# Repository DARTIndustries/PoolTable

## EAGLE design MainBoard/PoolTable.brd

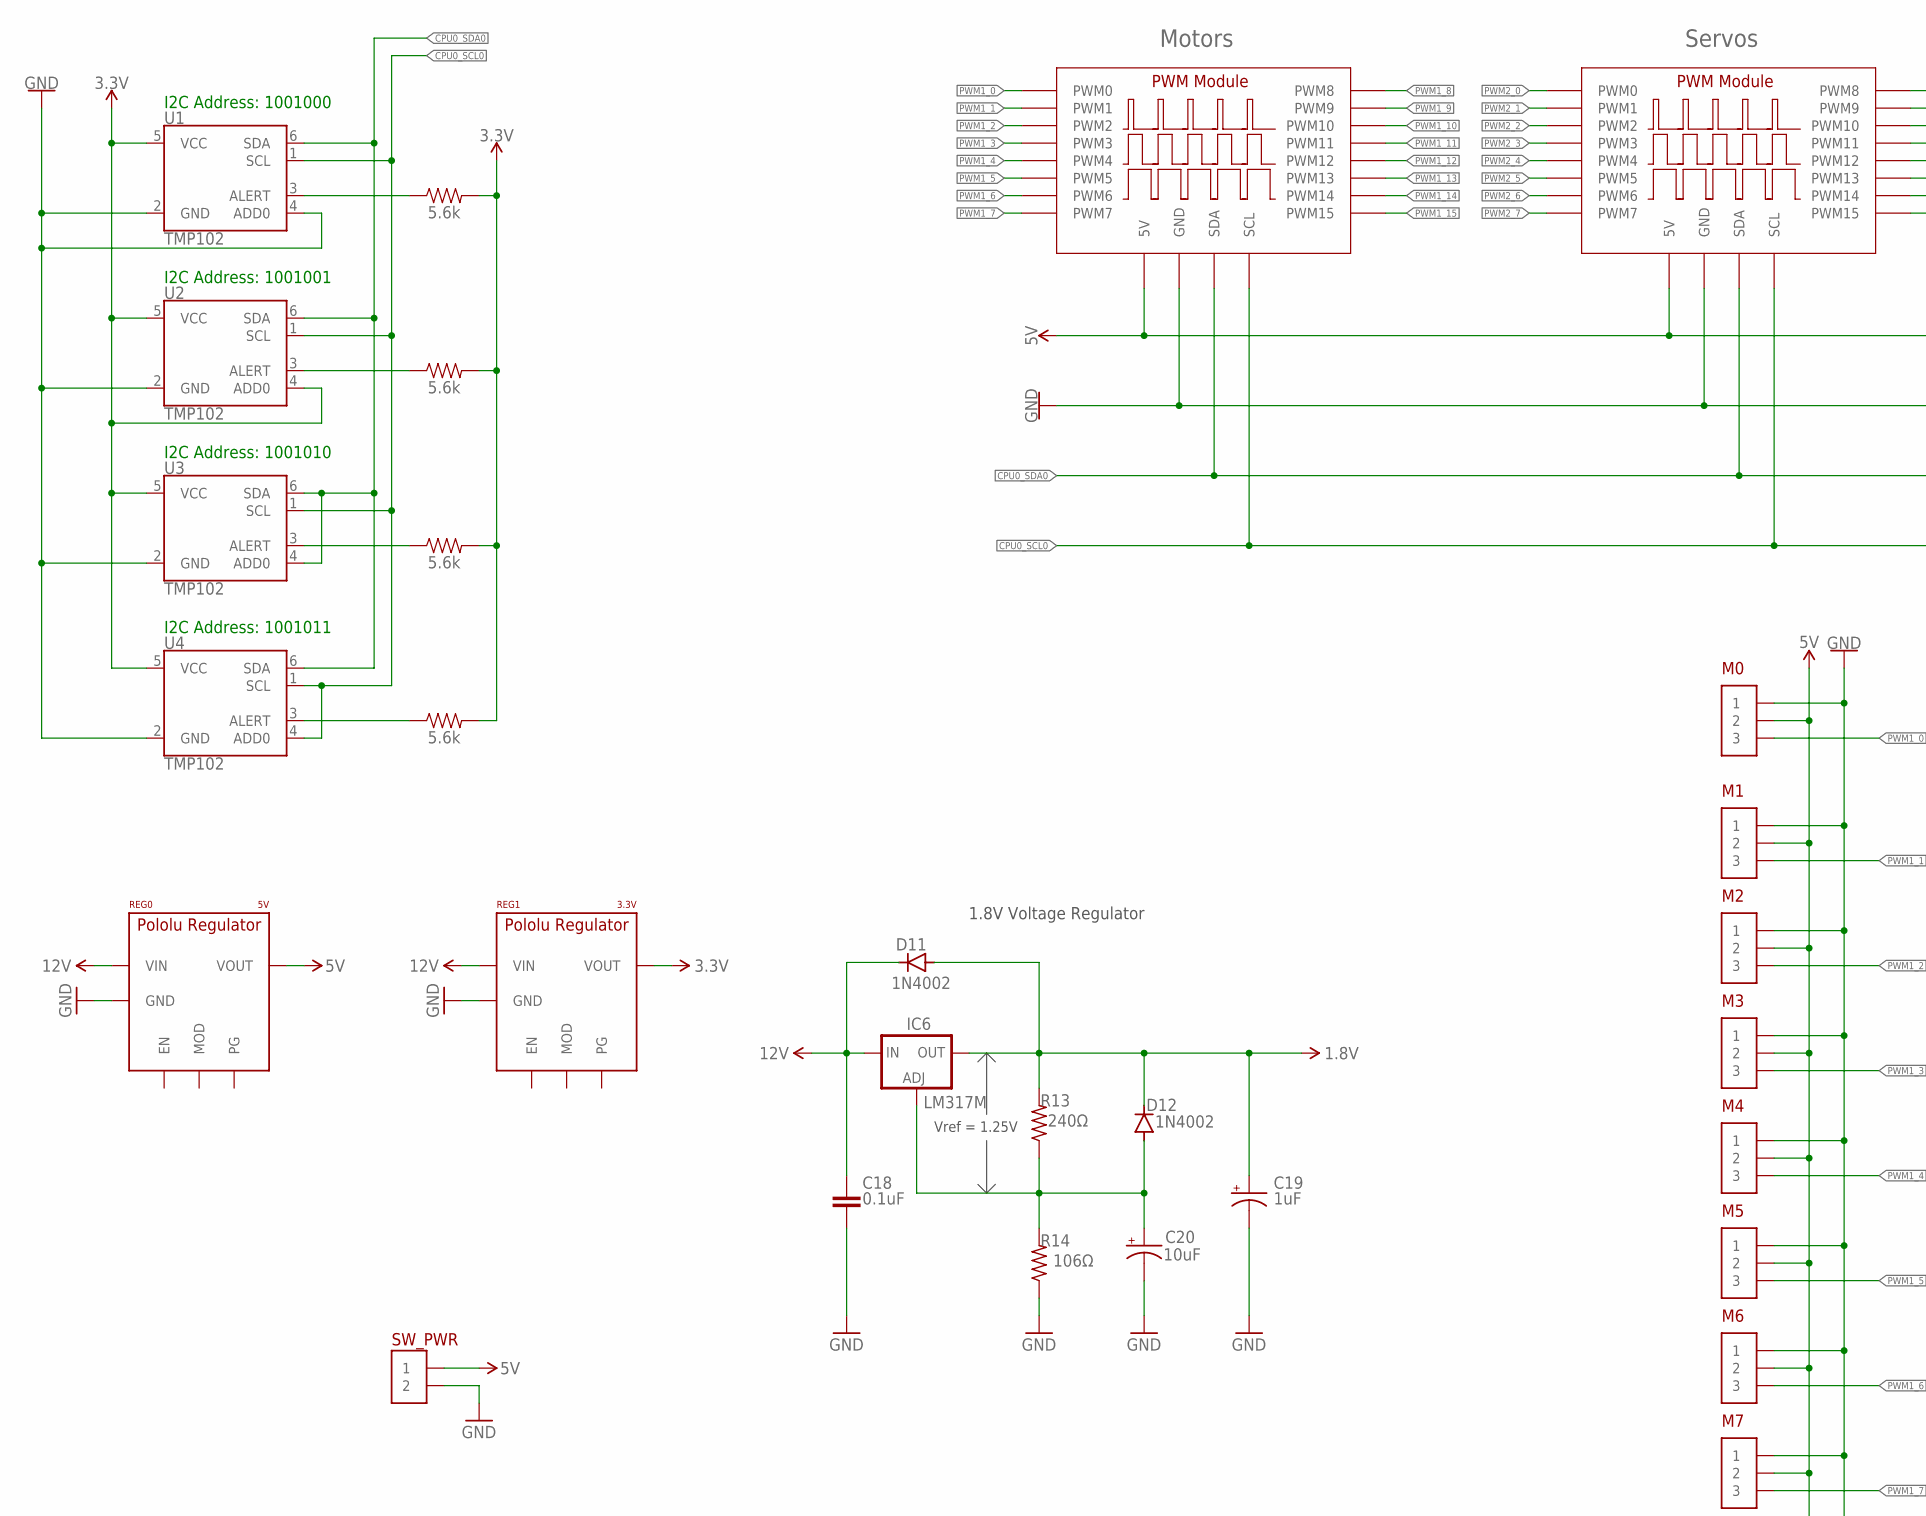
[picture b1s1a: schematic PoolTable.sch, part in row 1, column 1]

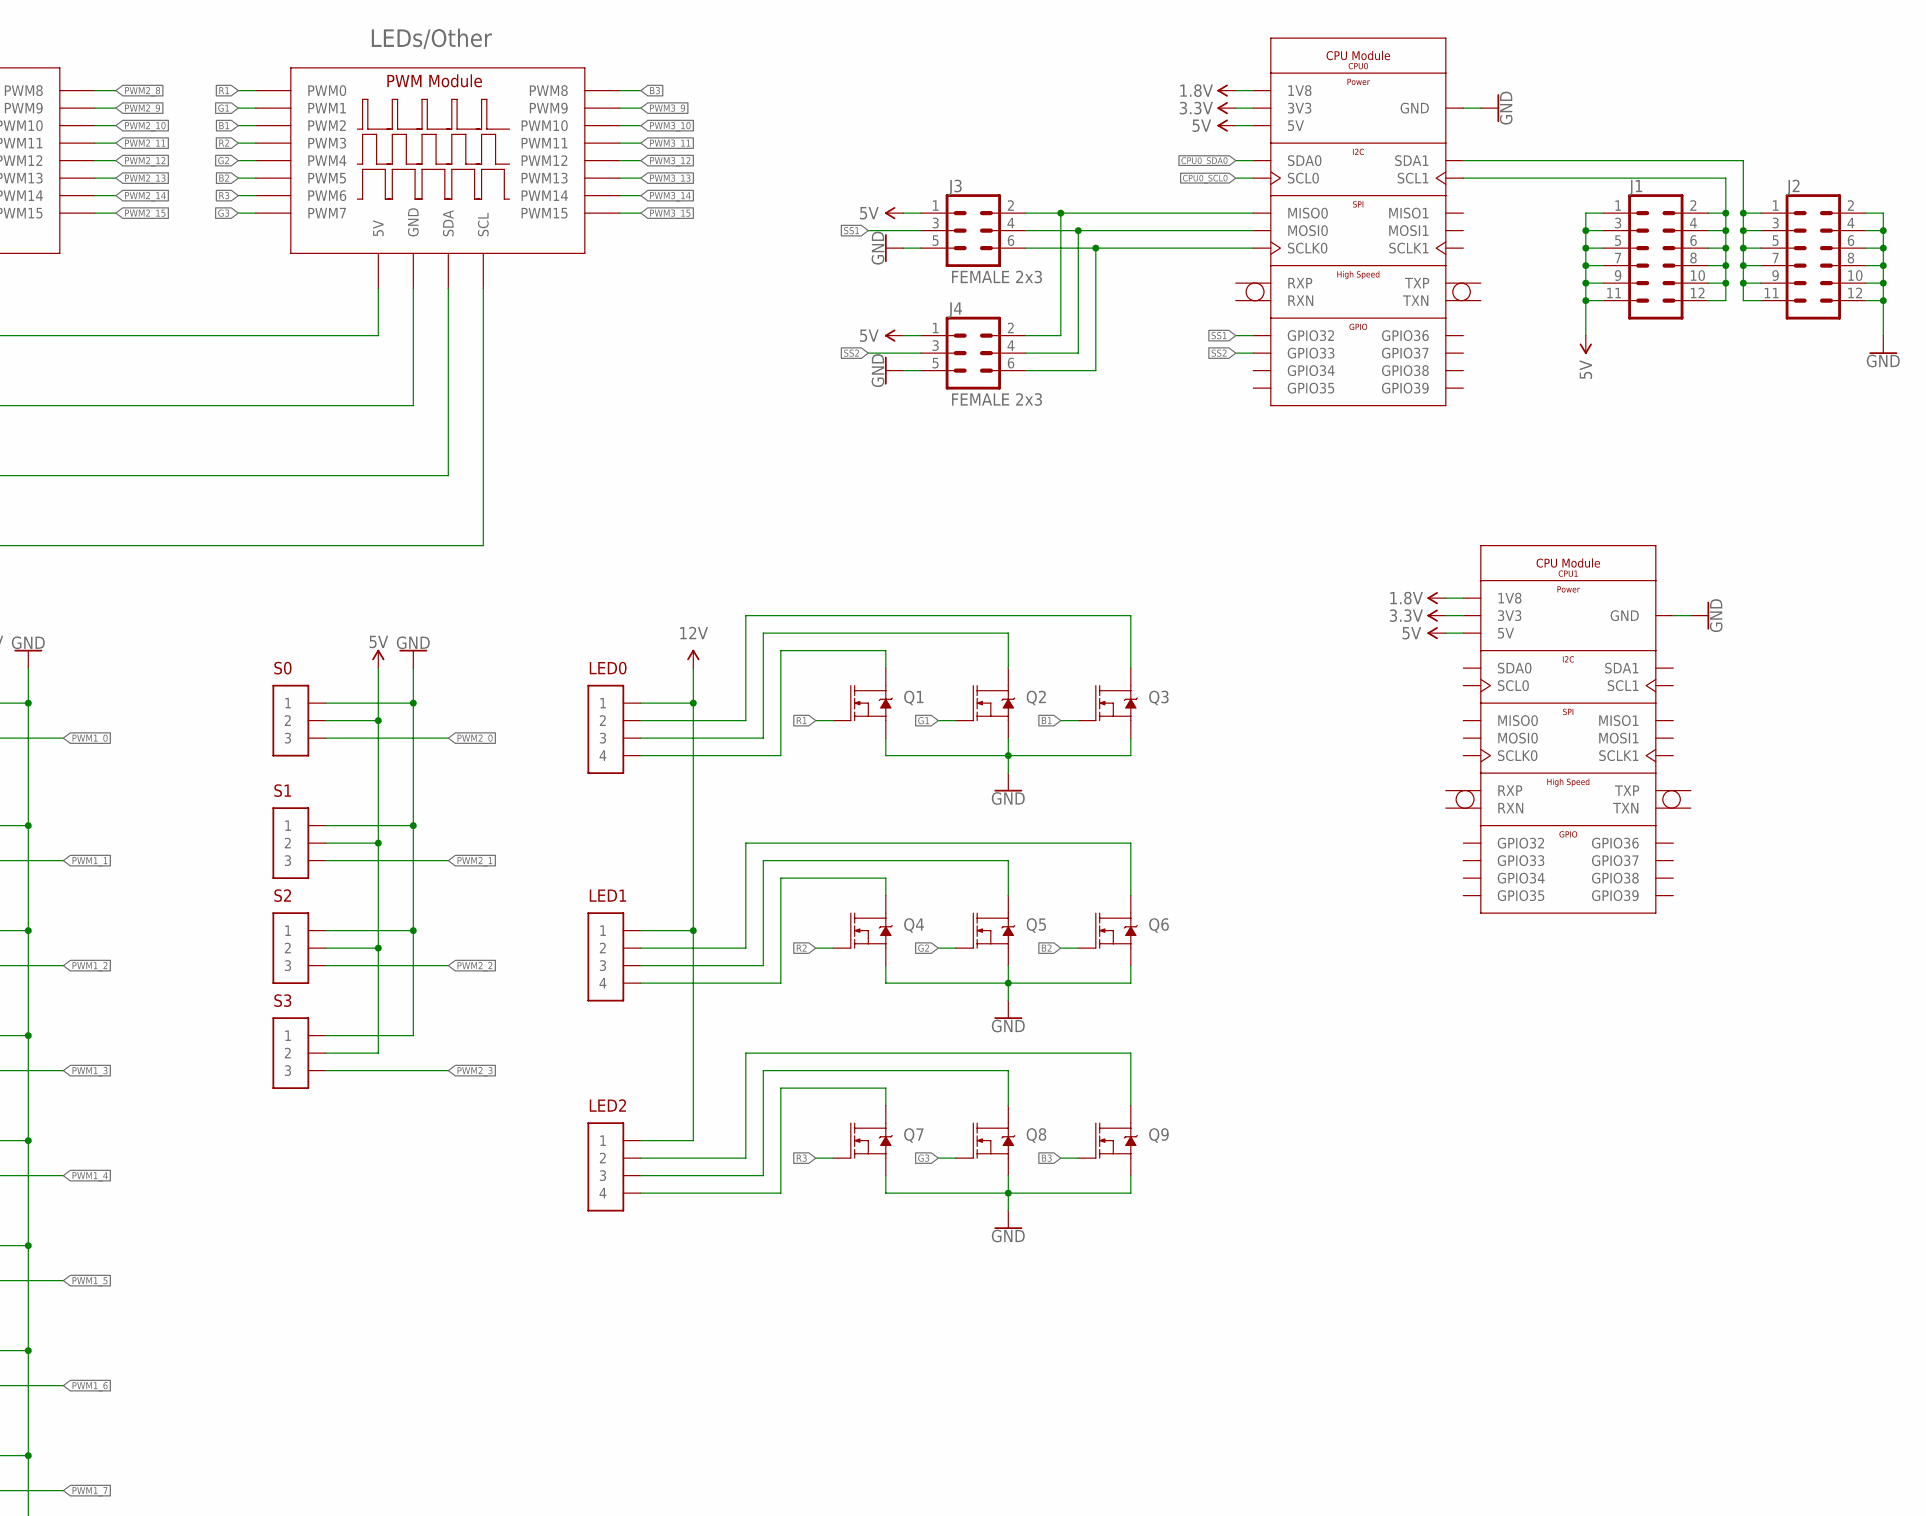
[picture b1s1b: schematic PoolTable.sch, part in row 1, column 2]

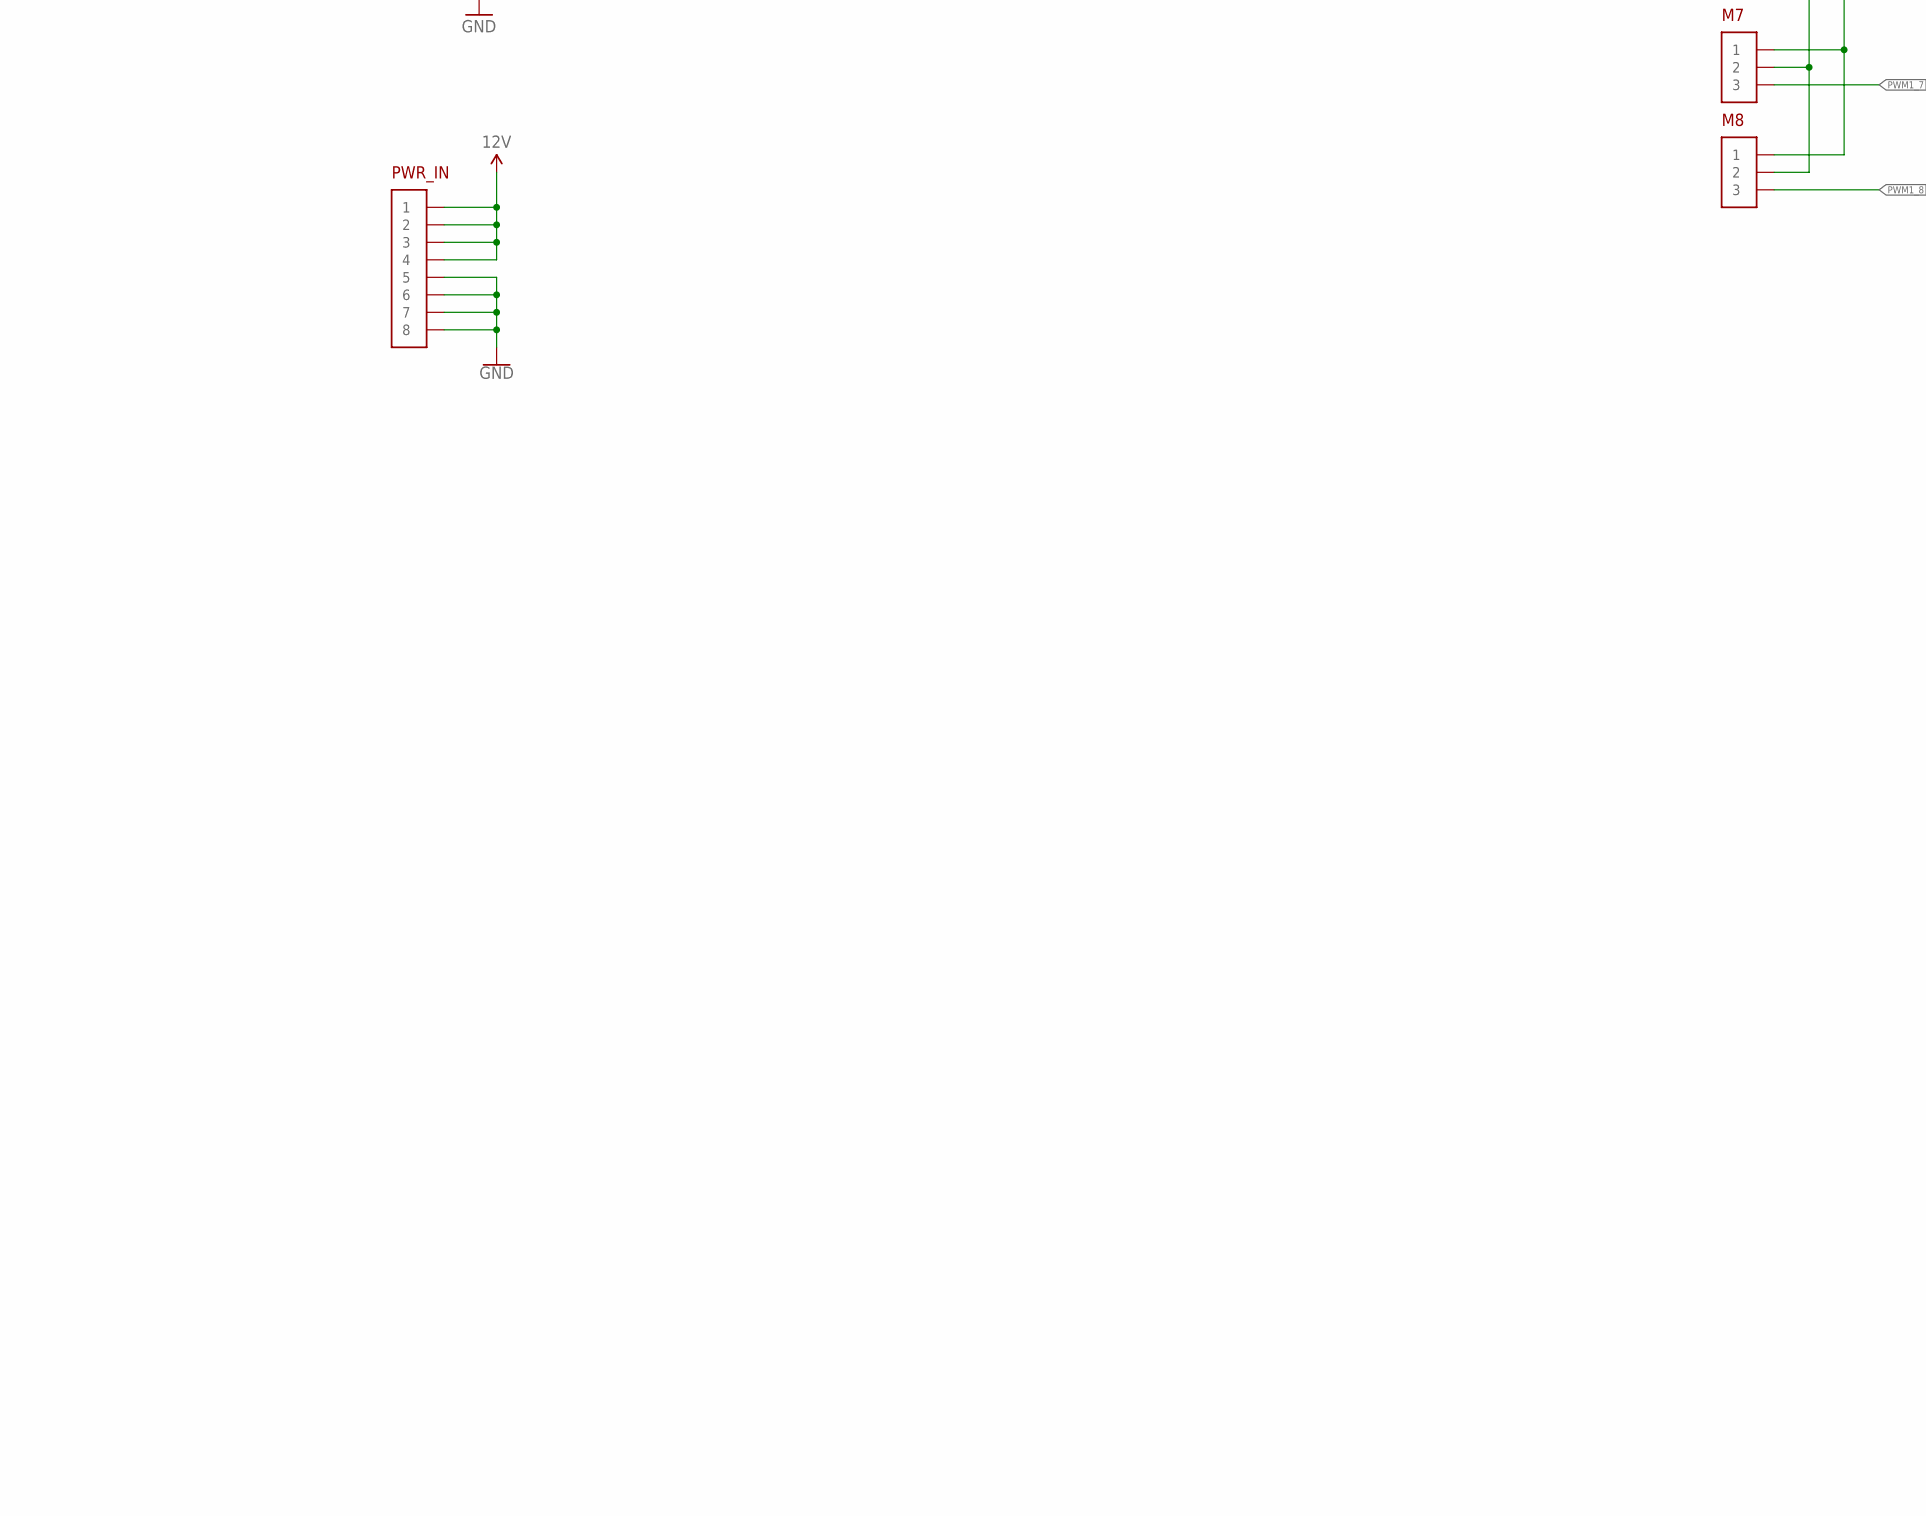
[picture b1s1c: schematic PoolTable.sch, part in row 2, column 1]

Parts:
C18: 0.1uF; C075-052X106
C19: 1uF; 085CS_1AR
C20: 10uF; 085CS_1AR
CPU0, CPU1: CPU_MODULE
D11, D12: 1N4002; DO41-10
IC6: LM317MBSTT3; SOT223; PARTNUMBER LM317M
J1, J2: 2X6 FEMALE; 2X6
J3, J4: FEMALE 2x3; 2X3
LED0, LED1, LED2: MOLEX-ULTRAFIT-1X04VERT; MOLEX-ULTRAFIT-1X04V
M0, M8: MOLEX-ULTRAFIT-1X03-VERT; MOLEX-ULTRAFIT-1X03V
M1, M2, M3, M4, M5, M6, M7: MOLEX-ULTRAFIT-1X03VERT; MOLEX-ULTRAFIT-1X03V
PWM0, PWM1, PWM2: PWM_MODULE
PWR_IN: MOLEX-ULTRAFIT-1X08
Q1, Q2, Q3, Q4, Q5, Q6, Q7, Q8, Q9: 60V/32A/35mΩ; TO220V
R9, R12, R15, R18: 5.6k; 0603
R13: 240Ω; M0805
R14: 106Ω; M0805
REG0: 5V; POLOLU-REG
REG1: 3.3V; POLOLU-REG
S0, S2, S3: MOLEX-ULTRAFIT-1X03VERT; MOLEX-ULTRAFIT-1X03V
S1: MOLEX-ULTRAFIT-1X03-VERT; MOLEX-ULTRAFIT-1X03V
SW_PWR: MOLEX-ULTRAFIT-1X02-HORIZ; MOLEX-ULTRAFIT-1X02H
U1, U2, U3, U4: TMP102; SOT563

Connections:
1.8V: C19.+, CPU0.19 (1V8), CPU1.19 (1V8), D11.A, D12.C, IC6.4 (OUT), R13.2
3.3V: CPU0.20 (3V3), CPU1.20 (3V3), R9.2, R12.2, R15.2, R18.2, REG1.P$4 (VOUT), REG1.P$7 (VOUT), REG1.P$8 (VOUT), U1.5 (VCC), U2.4 (ADD0), U2.5 (VCC), U3.5 (VCC), U4.5 (VCC)
5V: CPU0.18 (5V), CPU1.18 (5V), J1.1, J1.3, J1.5, J1.7, J1.9, J1.11, J3.1, J4.1, M0.P$2 (2), M1.P$2 (2), M2.P$2 (2), M3.P$2 (2), M4.P$2 (2), M5.P$2 (2), M6.P$2 (2), M7.P$2 (2), M8.P$2 (2), PWM0.5V, PWM1.5V, PWM2.5V, REG0.P$4 (VOUT), REG0.P$7 (VOUT), REG0.P$8 (VOUT), S0.P$2 (2), S1.P$2 (2), S2.P$2 (2), S3.P$2 (2), SW_PWR.P$1 (1)
12V: C18.1, D11.C, IC6.3 (IN), LED0.P$1 (1), LED1.P$1 (1), LED2.P$1 (1), PWR_IN.P$1 (1), PWR_IN.P$2 (2), PWR_IN.P$3 (3), PWR_IN.P$4 (4), REG0.P$1 (VIN), REG0.P$14 (VIN), REG0.P$15 (VIN), REG1.P$1 (VIN), REG1.P$14 (VIN), REG1.P$15 (VIN)
B1: PWM1.PWM2, Q3.1 (G)
B2: PWM1.PWM5, Q6.1 (G)
B3: PWM1.PWM8, Q9.1 (G)
CPU0_SCL0: CPU0.15 (SCL0), PWM0.SCL, PWM1.SCL, PWM2.SCL, U1.1 (SCL), U2.1 (SCL), U3.1 (SCL), U4.1 (SCL), U4.4 (ADD0)
CPU0_SDA0: CPU0.13 (SDA0), PWM0.SDA, PWM1.SDA, PWM2.SDA, U1.6 (SDA), U2.6 (SDA), U3.4 (ADD0), U3.6 (SDA), U4.6 (SDA)
G1: PWM1.PWM1, Q2.1 (G)
G2: PWM1.PWM4, Q5.1 (G)
G3: PWM1.PWM7, Q8.1 (G)
GND: C18.2, C19.-, C20.-, CPU0.1 (GND), CPU0.2 (GND), CPU0.3 (GND), CPU0.6 (GND), CPU0.7 (GND), CPU0.10 (GND), CPU0.11 (GND), CPU0.14 (GND), CPU0.17 (GND), CPU0.21 (GND), CPU0.24 (GND), CPU0.27 (GND), CPU0.30 (GND), CPU0.33 (GND), CPU0.37 (GND), CPU1.1 (GND), CPU1.2 (GND), CPU1.3 (GND), CPU1.6 (GND), CPU1.7 (GND), CPU1.10 (GND), CPU1.11 (GND), CPU1.14 (GND), CPU1.17 (GND), CPU1.21 (GND), CPU1.24 (GND), CPU1.27 (GND), CPU1.30 (GND), CPU1.33 (GND), CPU1.37 (GND), J2.2, J2.4, J2.6, J2.8, J2.10, J2.12, J3.5, J4.5, M0.P$1 (1), M1.P$1 (1), M2.P$1 (1), M3.P$1 (1), M4.P$1 (1), M5.P$1 (1), M6.P$1 (1), M7.P$1 (1), M8.P$1 (1), PWM0.GND, PWM1.GND, PWM2.GND, PWR_IN.P$5 (5), PWR_IN.P$6 (6), PWR_IN.P$7 (7), PWR_IN.P$8 (8), Q1.3 (S), Q2.3 (S), Q3.3 (S), Q4.3 (S), Q5.3 (S), Q6.3 (S), Q7.3 (S), Q8.3 (S), Q9.3 (S), R14.1, REG0.P$2 (GND), REG0.P$3 (GND), REG0.P$5 (GND), REG0.P$6 (GND), REG0.P$11 (GND), REG0.P$12 (GND), REG0.P$16 (GND), REG0.P$17 (GND), REG1.P$2 (GND), REG1.P$3 (GND), REG1.P$5 (GND), REG1.P$6 (GND), REG1.P$11 (GND), REG1.P$12 (GND), REG1.P$16 (GND), REG1.P$17 (GND), S0.P$1 (1), S1.P$1 (1), S2.P$1 (1), S3.P$1 (1), SW_PWR.P$2 (2), U1.2 (GND), U1.4 (ADD0), U2.2 (GND), U3.2 (GND), U4.2 (GND)
unnamed: LED0.P$4 (4), Q1.2 (D)
unnamed: LED0.P$3 (3), Q2.2 (D)
unnamed: LED0.P$2 (2), Q3.2 (D)
unnamed: CPU0.12 (SCL1), J1.2, J1.4, J1.6, J1.8, J1.10, J1.12
unnamed: CPU0.16 (SDA1), J2.1, J2.3, J2.5, J2.7, J2.9, J2.11
unnamed: R9.1, U1.3 (ALERT)
unnamed: C20.+, D12.A, IC6.1 (ADJ), R13.1, R14.2
unnamed: LED1.P$4 (4), Q4.2 (D)
unnamed: R12.1, U3.3 (ALERT)
unnamed: LED1.P$3 (3), Q5.2 (D)
unnamed: LED1.P$2 (2), Q6.2 (D)
unnamed: R15.1, U4.3 (ALERT)
unnamed: LED2.P$4 (4), Q7.2 (D)
unnamed: LED2.P$3 (3), Q8.2 (D)
unnamed: R18.1, U2.3 (ALERT)
unnamed: LED2.P$2 (2), Q9.2 (D)
unnamed: CPU0.39 (MISO0), J3.2, J4.2
unnamed: CPU0.40 (MOSI0), J3.4, J4.4
unnamed: CPU0.38 (SCLK0), J3.6, J4.6
PWM1_0: M0.P$3 (3), PWM0.PWM0
PWM1_1: M1.P$3 (3), PWM0.PWM1
PWM1_2: M2.P$3 (3), PWM0.PWM2
PWM1_3: M3.P$3 (3), PWM0.PWM3
PWM1_4: M4.P$3 (3), PWM0.PWM4
PWM1_5: M5.P$3 (3), PWM0.PWM5
PWM1_6: M6.P$3 (3), PWM0.PWM6
PWM1_7: M7.P$3 (3), PWM0.PWM7
PWM1_8: M8.P$3 (3), PWM0.PWM8
PWM1_9: PWM0.PWM9
PWM1_10: PWM0.PWM10
PWM1_11: PWM0.PWM11
PWM1_12: PWM0.PWM12
PWM1_13: PWM0.PWM13
PWM1_14: PWM0.PWM14
PWM1_15: PWM0.PWM15
PWM2_0: PWM2.PWM0, S0.P$3 (3)
PWM2_1: PWM2.PWM1, S1.P$3 (3)
PWM2_2: PWM2.PWM2, S2.P$3 (3)
PWM2_3: PWM2.PWM3, S3.P$3 (3)
PWM2_4: PWM2.PWM4
PWM2_5: PWM2.PWM5
PWM2_6: PWM2.PWM6
PWM2_7: PWM2.PWM7
PWM2_8: PWM2.PWM8
PWM2_9: PWM2.PWM9
PWM2_10: PWM2.PWM10
PWM2_11: PWM2.PWM11
PWM2_12: PWM2.PWM12
PWM2_13: PWM2.PWM13
PWM2_14: PWM2.PWM14
PWM2_15: PWM2.PWM15
PWM3_9: PWM1.PWM9
PWM3_10: PWM1.PWM10
PWM3_11: PWM1.PWM11
PWM3_12: PWM1.PWM12
PWM3_13: PWM1.PWM13
PWM3_14: PWM1.PWM14
PWM3_15: PWM1.PWM15
R1: PWM1.PWM0, Q1.1 (G)
R2: PWM1.PWM3, Q4.1 (G)
R3: PWM1.PWM6, Q7.1 (G)
SS1: CPU0.32 (GPIO32), J3.3
SS2: CPU0.31 (GPIO33), J4.3

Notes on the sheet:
I2C Address: 1001000
I2C Address: 1001001
I2C Address: 1001010
I2C Address: 1001011
Misc Components
1.8V Voltage Regulator
Vref = 1.25V
Motors
Servos
LEDs/Other

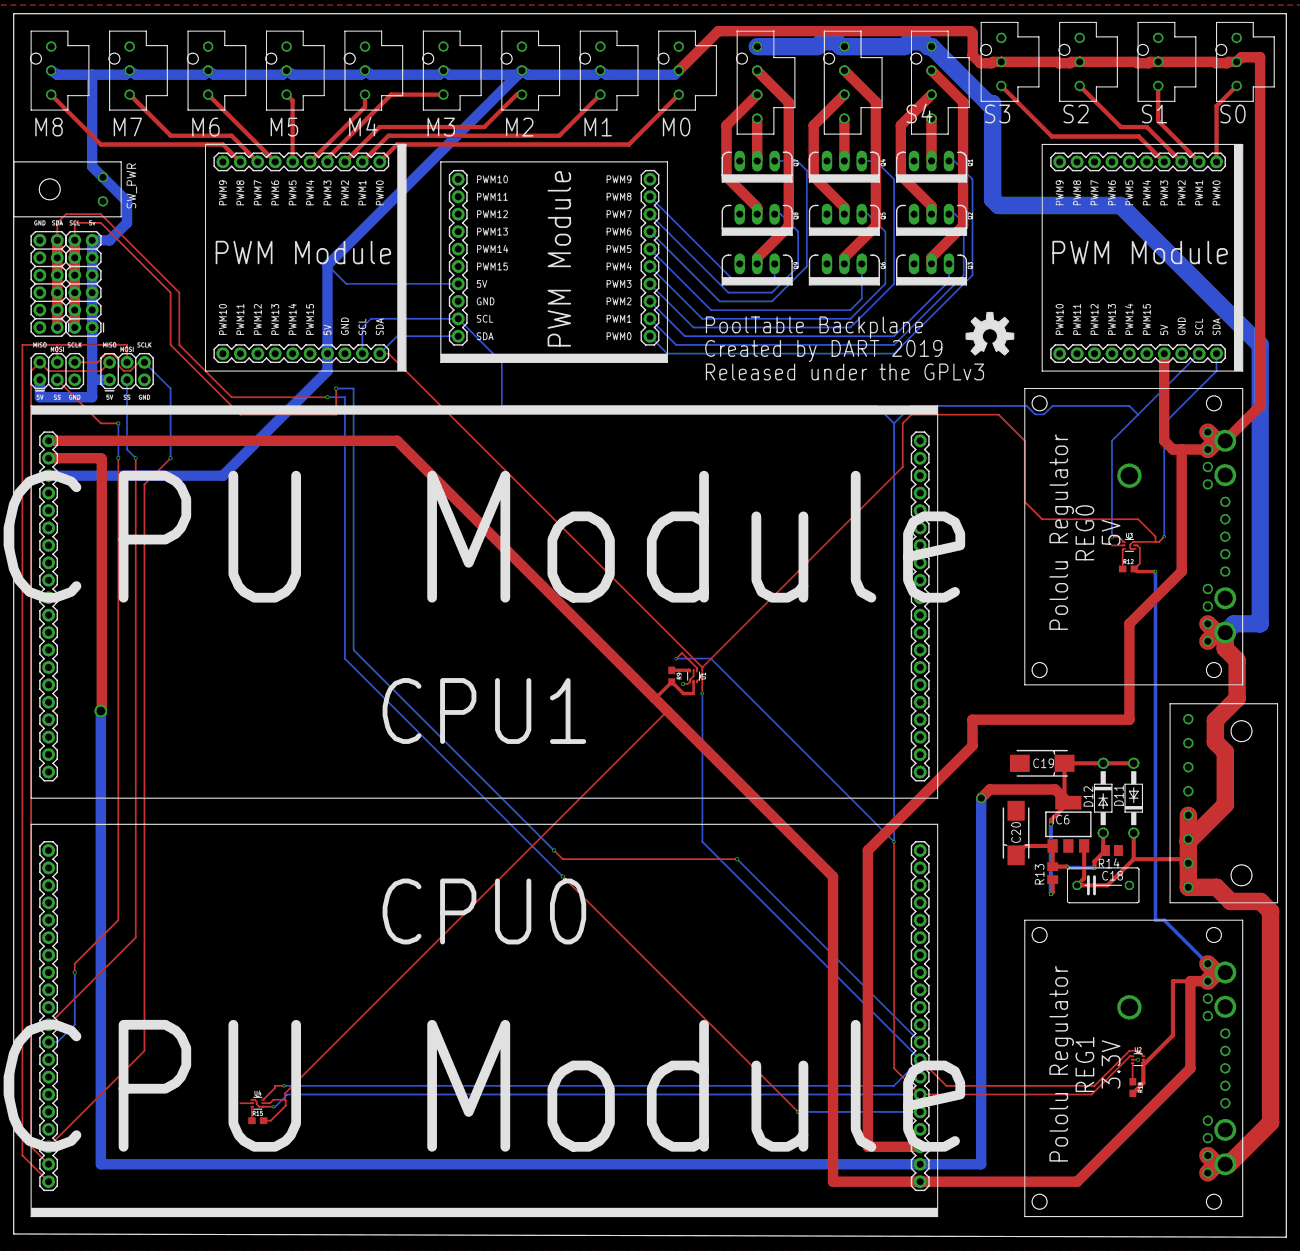
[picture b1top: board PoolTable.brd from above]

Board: 2 copper layers, 185.4 x 178.3 mm, 55 parts (0 on the bottom side), 50 nets.

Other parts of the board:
U$1: OSHW-LOGO-L

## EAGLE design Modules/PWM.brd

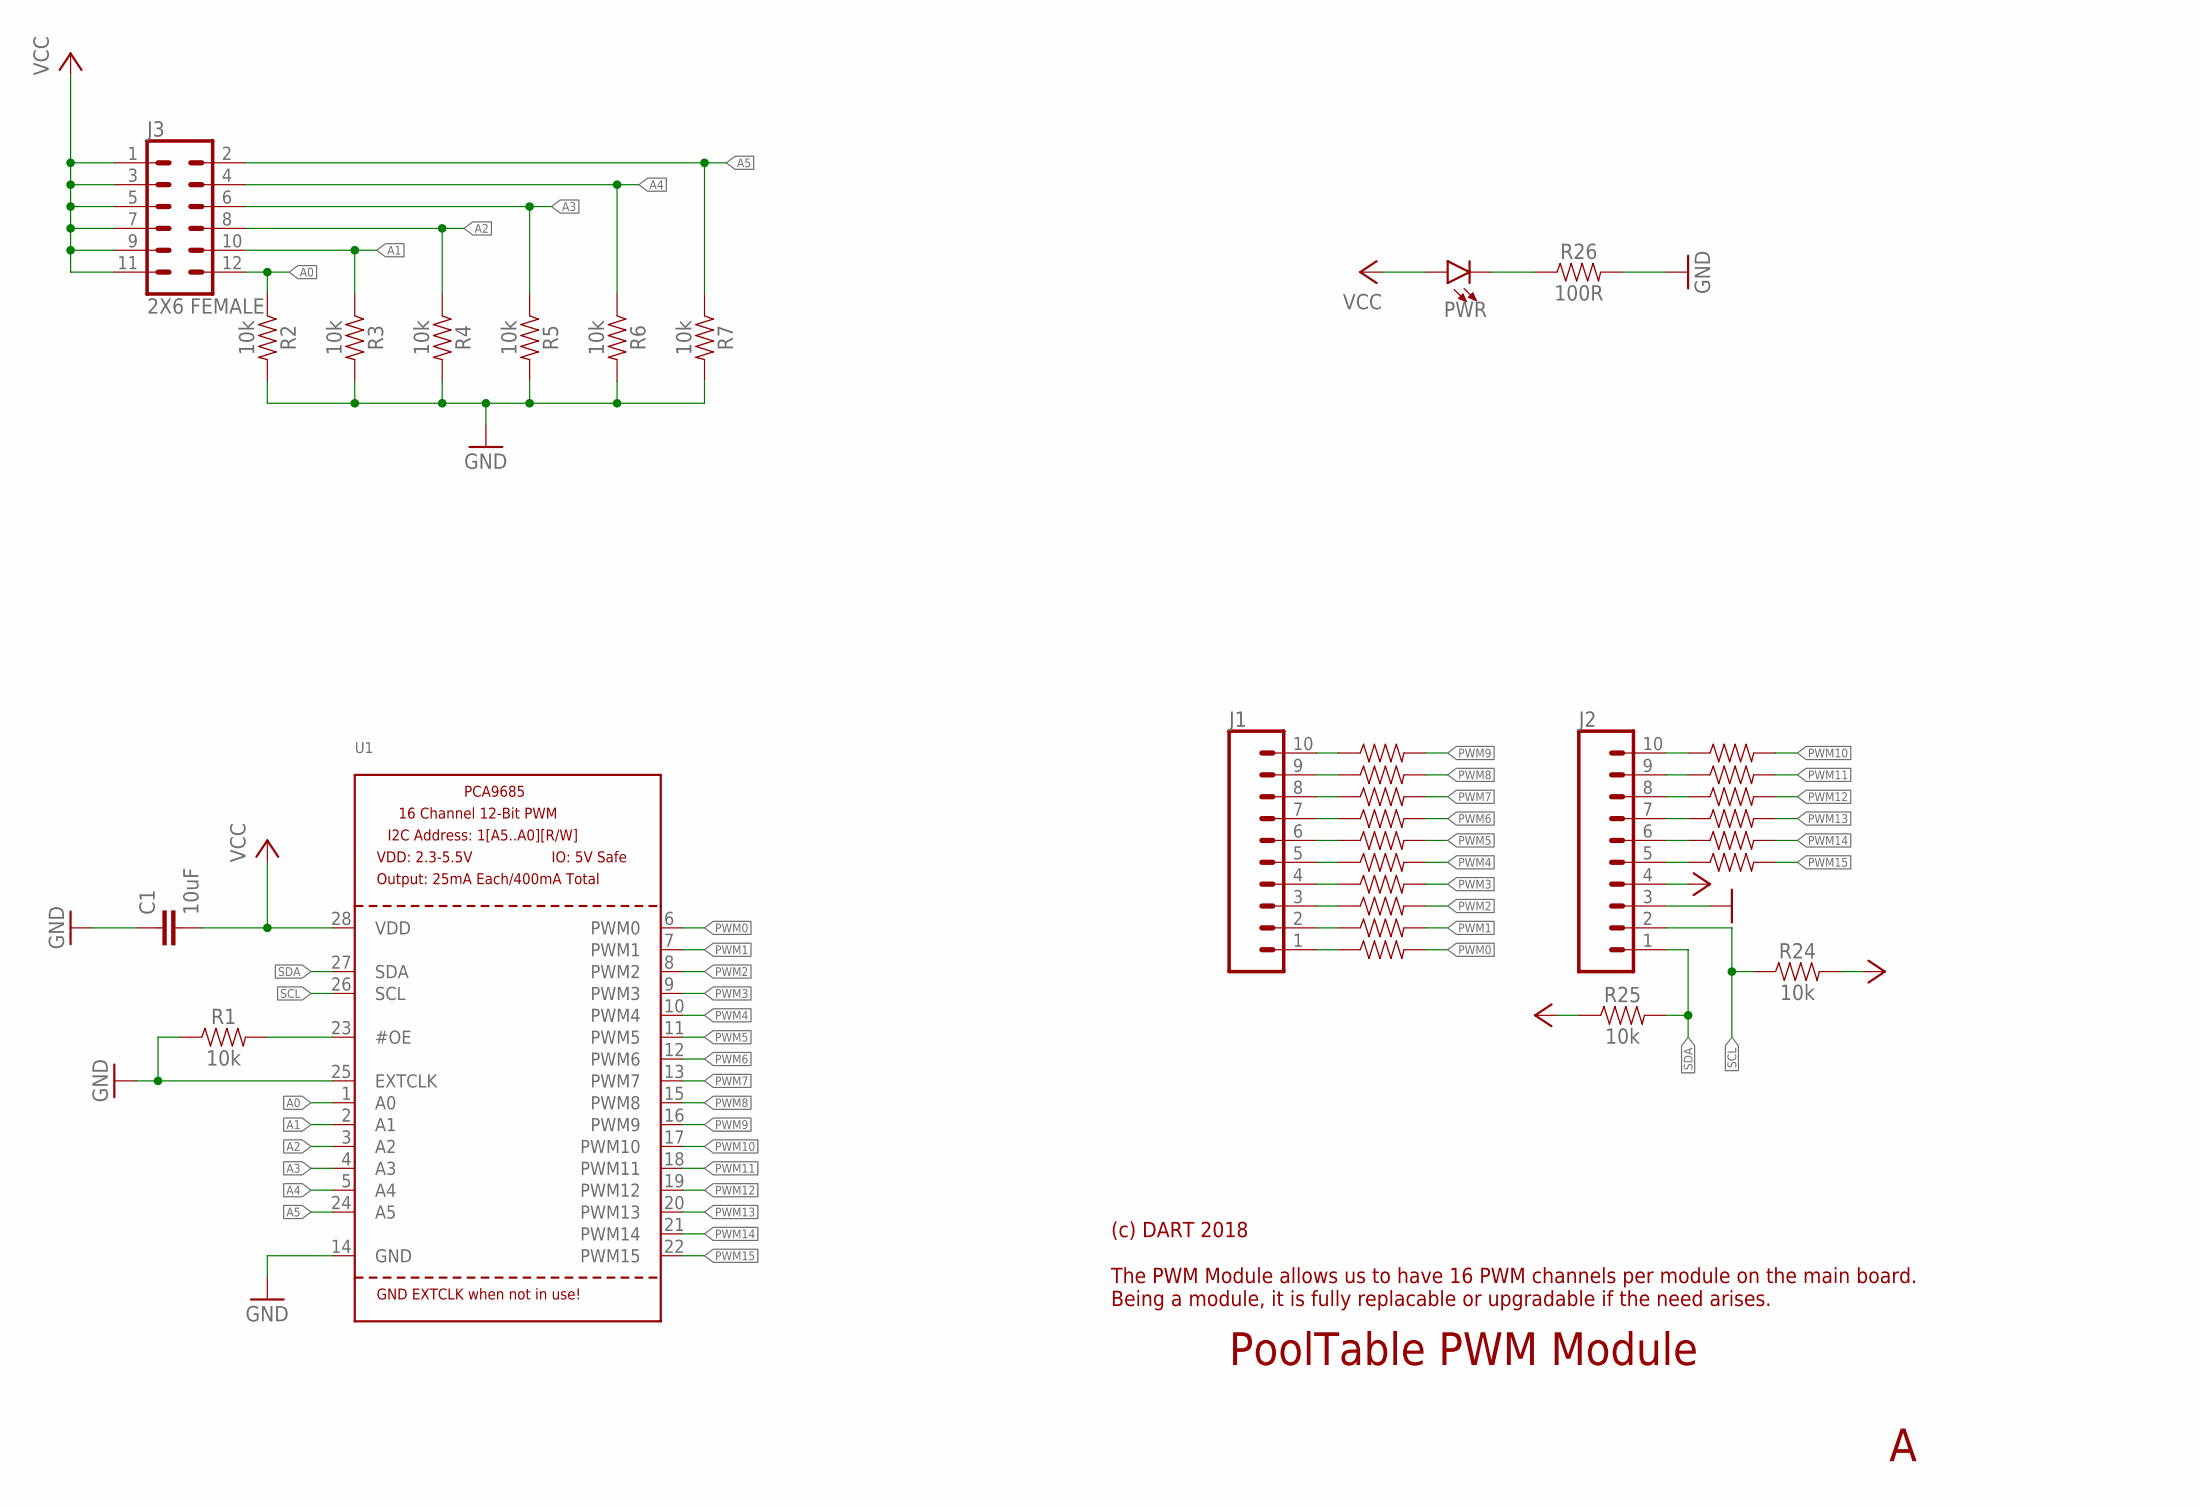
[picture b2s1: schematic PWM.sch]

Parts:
C1: 10uF; 0603
J1, J2: CONN_10"; 1X10
J3: 2X6 FEMALE; 2X6
PWR: LED0603; LED-0603
R1, R2, R3, R4, R5, R6, R7, R24, R25: 10k; 0603
R8, R9, R10, R11, R12, R13, R14, R15, R16, R17, R18, R19, R20, R21, R22, R23: 220; 0603
R26: 100R; 0603
U1: PCA9685; TSSOP28

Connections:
A0: J3.12, R2.1, U1.1 (A0)
A1: J3.10, R3.1, U1.2 (A1)
A2: J3.8, R4.1, U1.3 (A2)
A3: J3.6, R5.1, U1.4 (A3)
A4: J3.4, R6.1, U1.5 (A4)
A5: J3.2, R7.1, U1.24 (A5)
GND: C1.1, J2.3, R1.1, R2.2, R3.2, R4.2, R5.2, R6.2, R7.2, R26.2, U1.14 (GND), U1.25 (EXTCLK)
unnamed: R1.2, U1.23 (#OE)
unnamed: J1.10, R8.1
unnamed: J1.9, R9.1
unnamed: J1.8, R10.1
unnamed: J1.7, R11.1
unnamed: J1.6, R12.1
unnamed: J1.5, R13.1
unnamed: J1.4, R14.1
unnamed: J1.3, R15.1
unnamed: J1.2, R16.1
unnamed: J1.1, R17.1
unnamed: J2.10, R18.1
unnamed: J2.9, R19.1
unnamed: J2.8, R20.1
unnamed: J2.7, R21.1
unnamed: J2.6, R22.1
unnamed: J2.5, R23.1
unnamed: PWR.C, R26.1
PWM0: R17.2, U1.6 (PWM0)
PWM1: R16.2, U1.7 (PWM1)
PWM2: R15.2, U1.8 (PWM2)
PWM3: R14.2, U1.9 (PWM3)
PWM4: R13.2, U1.10 (PWM4)
PWM5: R12.2, U1.11 (PWM5)
PWM6: R11.2, U1.12 (PWM6)
PWM7: R10.2, U1.13 (PWM7)
PWM8: R9.2, U1.15 (PWM8)
PWM9: R8.2, U1.16 (PWM9)
PWM10: R18.2, U1.17 (PWM10)
PWM11: R19.2, U1.18 (PWM11)
PWM12: R20.2, U1.19 (PWM12)
PWM13: R21.2, U1.20 (PWM13)
PWM14: R22.2, U1.21 (PWM14)
PWM15: R23.2, U1.22 (PWM15)
SCL: J2.2, R24.1, U1.26 (SCL)
SDA: J2.1, R25.2, U1.27 (SDA)
VCC: C1.2, J2.4, J3.1, J3.3, J3.5, J3.7, J3.9, J3.11, PWR.A, R24.2, R25.1, U1.28 (VDD)

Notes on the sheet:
PoolTable PWM Module
(c) DART 2018 The PWM Module allows us to have 16 PWM channels per module on the main board. Being a module, it is fully replacable or upgradable if the need arises.

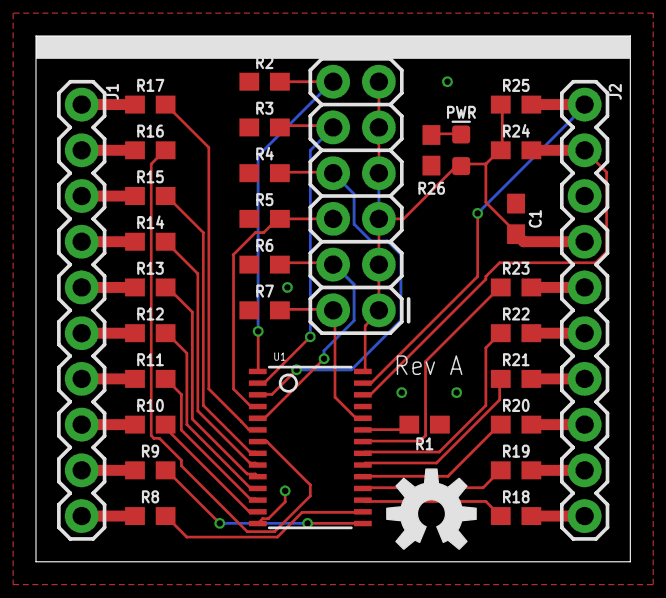
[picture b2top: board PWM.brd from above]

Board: 2 copper layers, 33.0 x 29.2 mm, 33 parts (0 on the bottom side), 44 nets.

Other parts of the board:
U$1: OSHW-LOGO-M

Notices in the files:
MainBoard/PoolTable.brd:
Released under the GPLv3
parts and their libraries:
SparkFun-Resistors: Licensing: Creative Commons ShareAlike 4.0 International - https://creativecommons.org/licenses/by-sa/4.0
